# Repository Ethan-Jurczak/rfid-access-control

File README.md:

# rfid-access-control
stm32 based RFID system.
# Specs
- Runs off a STM32f411ret arm microcontroller with a EM4095 for the RFID demodulation and writing modulation.
- Includes a USB-C receptacle for both power and data transfer to the STM32
- Includes a 4 pin connecter for programing with a STlink
- 520 uH coil connected in series accross 4 layers to minimize space while maximising Q
# Schematics
- [RFID-Read-Write-Schematic.pdf](https://github.com/user-attachments/files/28185533/RFID-Read-Write-Schematic.pdf)

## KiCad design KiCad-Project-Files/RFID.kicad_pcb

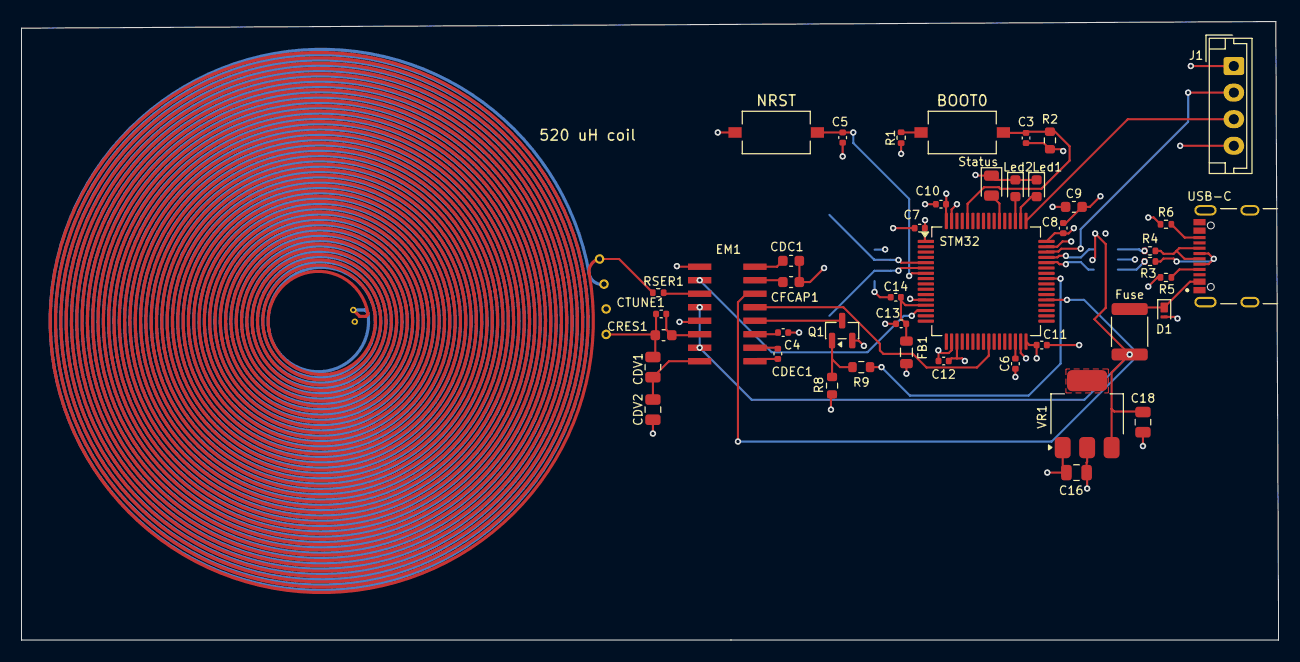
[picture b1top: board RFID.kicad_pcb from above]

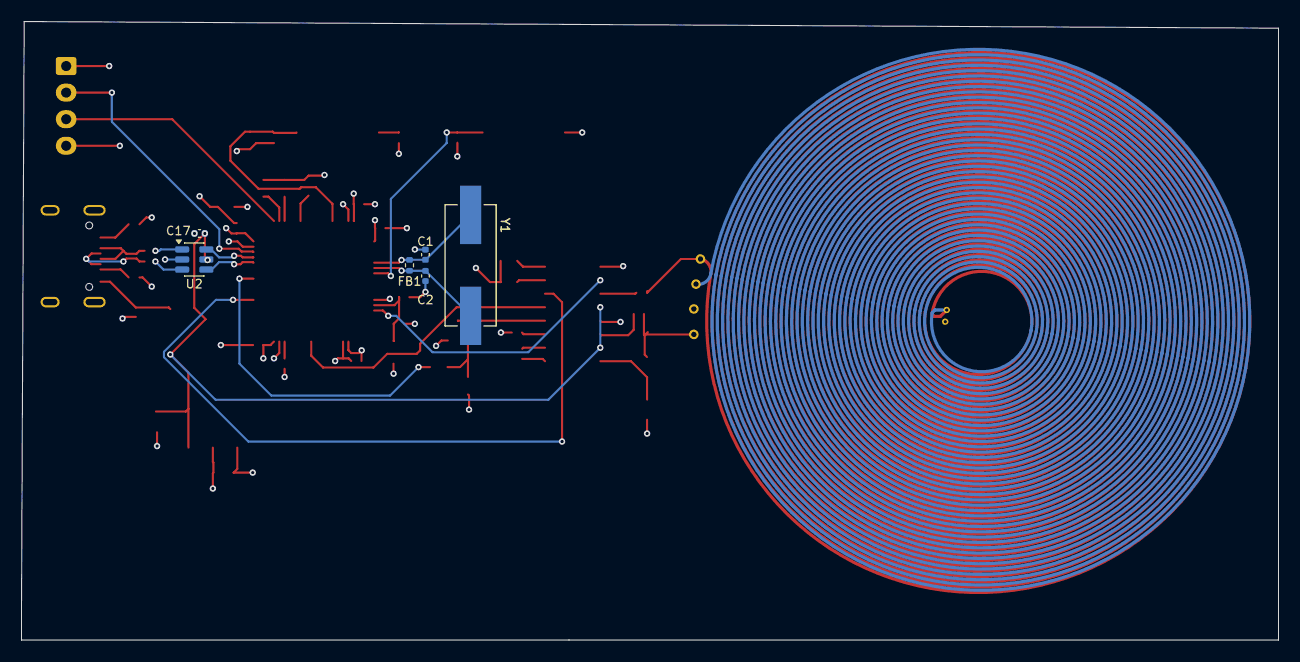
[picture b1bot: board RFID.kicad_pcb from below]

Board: 4 copper layers, 118.2 x 58.2 mm, 51 parts (6 on the bottom side), 36 nets.

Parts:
520 uH coil: 520 uH coil
BOOT0: SW_Push; SW_Tactile_SPST_NO_Straight_CK_PTS636Sx25SMTRLFS
C1, C2: 33 pF; C_0402_1005Metric
C3, C5, C7, C9, C10, C11, C12, C14, C17: 100nF; C_0402_1005Metric
C4: 150nF; C_0402_1005Metric
C6: 1 uF; C_0402_1005Metric
C8: 4.7uF; C_0603_1608Metric
C13: 1uF; C_0402_1005Metric
C16, C18: 10 uF; C_0805_2012Metric
CDC1: 10nF; C_0603_1608Metric
CDEC1: 100nF; C_0402_1005Metric
CDV1: 56pF; C_0805_2012Metric
CDV2: 1.5nF; C_0805_2012Metric
CFCAP1: 10nF; C_0603_1608Metric
CRES1: 3nF; C_0603_1608Metric
CTUNE1: ?pF; C_0402_1005Metric
D1: PTVS5V0Z1USK; Nexperia_DSN1608-2_1.6x0.8mm
EM1: SO16
FB1: 600 Ohm @ 100mHz; L_0805_2012Metric
FB1#2: 1M Ohm; R_0402_1005Metric
Fuse: MF-MSMF050-2; Fuse_1812_4532Metric
J1: Conn_01x04_Pin; JST_EH_B4B-EH-A_1x04_P2.50mm_Vertical
Led1, Led2: LED; LED_0603_1608Metric
NRST: SW_Push; SW_Tactile_SPST_NO_Straight_CK_PTS636Sx25SMTRLFS
Q1: 2N7002; SOT-23
R1: 100 Ohm; R_0402_1005Metric
R2, R8: 10k Ohm; R_0603_1608Metric
R3, R4: 22 Ohm; R_0402_1005Metric
R5, R6: 5.1k Ohm; R_0402_1005Metric
R9: 100 Ohm; R_0603_1608Metric
RSER1: 33Ohm; R_0402_1005Metric
STM32: STM32F411RETx; LQFP-64_10x10mm_P0.5mm
Status: LED; LED_0805_2012Metric
U2: USBLC6; SOT-23-6
USB-C: USB_C_Receptacle; SAMESKY_UJ20-C-H-G-SMT-1-P16-TR
VR1: LM1117MPX-3.3_NOPB; SOT-223-3_TabPin2
Y1: ECS-80-20-5PXDU-TR; XTAL_ECS-80-20-5PXDU-TR

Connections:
+3.3V: C7.2, C8.2, C9.2, C10.2, C11.2, C12.2, C16.1, FB1.2, J1.1, R1.1, STM32.1 (VBAT), STM32.19 (VDD), STM32.32 (VDD), STM32.48 (VDD), STM32.64 (VDD), VR1.2 (VOUT_2)
+5V: C17.1, C18.1, EM1.4 (DVDD), EM1.7 (VDD), Fuse.1, U2.5 (VBUS), VR1.3 (VIN)
/BOOT0: BOOT0.2, C3.1, R2.1, STM32.60 (BOOT0)
/D+: R4.1, R4.2, STM32.45 (PA12), U2.1 (I/O1), U2.6 (I/O1), USB-C.A6 (D+), USB-C.B6 (D+)
/D-: R3.1, R3.2, STM32.44 (PA11), U2.3 (I/O2), U2.4 (I/O2), USB-C.A7 (D-), USB-C.B7 (D-)
/NRST: C5.1, NRST.2, STM32.7 (NRST)
/OSC_IN: C1.2, FB1#2.1, STM32.5 (PH0), Y1.1
/OSC_OUT: C2.1, FB1#2.2, STM32.6 (PH1), Y1.2
/SWCLK: J1.3, STM32.49 (PA14)
/SWDIO: J1.2, STM32.46 (PA13)
/VBUS: D1.1 (K), Fuse.2, USB-C.A4_B9
/VDDA: C13.1, C14.1, FB1.1, STM32.13 (VDDA)
GND: C1.1, C2.2, C3.2, C4.2, C5.2, C6.2, C7.1, C8.1, C9.1, C10.1, C11.1, C12.1, C13.2, C14.2, C16.2, C17.2, C18.2, CDC1.2, CDV2.2, CFCAP1.2, D1.2 (A), EM1.1 (VSS), EM1.5 (DVSS), J1.4, Led1.1 (K), Led2.1 (K), NRST.1, Q1.2 (S), R2.2, R5.1, R6.1, R8.1, STM32.12 (VSSA), STM32.18 (VSS), STM32.31 (VSS), STM32.47 (VSS), STM32.63 (VSS), Status.1 (K), U2.2 (GND), VR1.1 (GND)
unnamed: Led1.2 (A), STM32.50 (PA15)
unnamed: Led2.2 (A), STM32.51 (PC10)
unnamed: CDV1.1, CRES1.1, CTUNE1.1
unnamed: C4.1, EM1.11 (AGND)
unnamed: EM1.3 (ANT1), RSER1.2
unnamed: CRES1.2, CTUNE1.2, EM1.6 (ANT2)
unnamed: CDEC1.1, EM1.10 (CDEC_In)
unnamed: CDEC1.2, EM1.9 (CDEC_Out)
unnamed: CDC1.1, EM1.16 (DC2)
unnamed: CDV1.2, CDV2.1, EM1.8 (DMOD-IN)
unnamed: EM1.13 (DMOD_Out), STM32.25 (PC5)
unnamed: CFCAP1.1, EM1.15 (FCAP)
unnamed: EM1.12 (MOD), Q1.3 (D)
unnamed: EM1.2 (RDY/CLK), STM32.14 (PA0)
unnamed: EM1.14 (SHD), STM32.37 (PC6)
unnamed: R5.2, USB-C.A5 (CC1)
unnamed: R6.2, USB-C.B5 (CC2)
unnamed: 520 uH coil.1, RSER1.1
unnamed: Q1.1 (G), R8.2, R9.2
unnamed: BOOT0.1, R1.2
unnamed: STM32.54 (PD2), Status.2 (A)
unnamed: R9.1, STM32.41 (PA8)
unnamed: C6.1, STM32.30 (VCAP1)

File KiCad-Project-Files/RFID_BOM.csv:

"Reference","Qty","Value","DNP","Exclude from BOM","Exclude from Board","Footprint","Datasheet"
"AccessLed1,AccessLed2","2","LED","","","","LED_SMD:LED_0603_1608Metric",""
"C1,C2","2","33 pF","","","","Capacitor_SMD:C_0402_1005Metric",""
"C3,C5,C7,C9,C10,C11,C12,C14,C17,CDEC1","10","100nF","","","","Capacitor_SMD:C_0402_1005Metric",""
"C4","1","150nF","","","","Capacitor_SMD:C_0402_1005Metric",""
"C6","1","1 uF","","","","Capacitor_SMD:C_0402_1005Metric",""
"C8","1","4.7uF","","","","Capacitor_SMD:C_0603_1608Metric",""
"C13","1","1uF","","","","Capacitor_SMD:C_0402_1005Metric",""
"C16,C18","2","10 uF","","","","Capacitor_SMD:C_0805_2012Metric",""
"CDC1,CFCAP1","2","10nF","","","","Capacitor_SMD:C_0603_1608Metric",""
"CDV1","1","56pF","","","","Capacitor_SMD:C_0805_2012Metric",""
"CDV2","1","1.5nF","","","","Capacitor_SMD:C_0805_2012Metric",""
"CRES1","1","3nF","","","","Capacitor_SMD:C_0603_1608Metric",""
"CTUNE1","1","?pF","","","","Capacitor_SMD:C_0402_1005Metric",""
"D1","1","PTVS5V0Z1USK","","","","Diode_SMD:Nexperia_DSN1608-2_1.6x0.8mm","https://assets.nexperia.com/documents/data-sheet/PTVS5V0Z1USK.pdf"
"EM1","1","","","","","EM4095:SO16",""
"F1","1","MF-MSMF050-2","","","","Fuse:Fuse_1812_4532Metric",""
"FB1","1","600 Ohm @ 100mHz","","","","Inductor_SMD:L_0805_2012Metric",""
"J1","1","Conn_01x04_Pin","","","","Connector_JST:JST_EH_B4B-EH-A_1x04_P2.50mm_Vertical",""
"J2","1","USB_C_Receptacle","","","","EM4095:SAMESKY_UJ20-C-H-G-SMT-1-P16-TR","https://www.usb.org/sites/default/files/documents/usb_type-c.zip"
"LA1","1","520uH","","","","",""
"Q1","1","2N7002","","","","Package_TO_SOT_SMD:SOT-23","https://www.onsemi.com/pub/Collateral/NDS7002A-D.PDF"
"R1","1","100 Ohm","","","","Resistor_SMD:R_0402_1005Metric",""
"R2,R8","2","10k Ohm","","","","Resistor_SMD:R_0603_1608Metric",""
"R3,R4","2","22 Ohm","","","","Resistor_SMD:R_0402_1005Metric",""
"R5,R6","2","5.1k Ohm","","","","Resistor_SMD:R_0402_1005Metric",""
"R9","1","100 Ohm","","","","Resistor_SMD:R_0603_1608Metric",""
"RSER1","1","33Ohm","","","","Resistor_SMD:R_0402_1005Metric",""
"R_FB1","1","1M Ohm","","","","Resistor_SMD:R_0402_1005Metric",""
"Status1","1","LED","","","","LED_SMD:LED_0805_2012Metric",""
"SW1,SW2","2","SW_Push","","","","Button_Switch_SMD:SW_Tactile_SPST_NO_Straight_CK_PTS636Sx25SMTRLFS",""
"U1","1","STM32F411RETx","","","","Package_QFP:LQFP-64_10x10mm_P0.5mm","https://www.st.com/resource/en/datasheet/stm32f411re.pdf"
"U2","1","USBLC6","","","","Package_TO_SOT_SMD:SOT-23-6","https://www.st.com/resource/en/datasheet/usblc6-2.pdf"
"VR1","1","LM1117MPX-3.3_NOPB","","","","Package_TO_SOT_SMD:SOT-223-3_TabPin2",""
"Y1","1","ECS-80-20-5PXDU-TR","","","","EM4095:XTAL_ECS-80-20-5PXDU-TR",""

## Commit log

2026-05-13 Create docs
2026-05-13 Create .gitkeep for docs
2026-05-24 Create KiCad-Project-Files folder
2026-05-24 Add All KiCad project files
    current as of 5/23/26
